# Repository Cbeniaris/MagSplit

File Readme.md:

# MagSplit
A wired split keyboard with ATmega32u4 promicro microcontrollers, oled displays, and magnetic connectors for module attachment

## Overview
MagSplit is an extension of my Beniaris46 keyboard featuring an extra column for each hand, much like a Corne board, and magnetic connectors for attaching "modules".  I made a few macropads that supported qmk and got frustrated when each one needed a new cable on my desk.   I wanted a modular system that allow attaching "modules" with different configuations for different workflows. Modules connect to the main keyboard via the magnetic connector on the side of the left split of the keyboard.  The magnetic connector handles ESD for the exposed pins as well as load switching for power delivery.  The modules themselves communicate over UART to the main half of the keyboard, notifying it of a successful connection, and relaying keypresses through to the host. Since each module is still a qmk board with the same ATmega32u4 micros, they still function as standalone HID boards. They retain their layers, macros, etc. when swapping hosts.  This allows for quickly snapping a new module on without needing to fetch a cable. 

## MODULE POWER WARNING
THERE IS NO BACK FEED PROTECTION FOR THE 5V RAIL.  You can plug in the usb and connect the module with the magnetic connector.  In an effort to keep complexity low and cost down, I did not include this.  The simple rule is: "One or the other". DO NOT attach both the magnetic connector to the main half of the keyboard AND the module to usb-c power at the same time. I had initially planned to use Schottky diodes to prevent this but worried about voltage drop for modules.

## Materials
| Component | Part Number |
| --- | --- |
| Micro | Any ATmega32ur pro micro |
| 3 pin TRS Jack | HC-PJ-320A-3P-D |
| Load Switch | TPS2552DBV (SOT-23-6, not WSON)|
| ESD protection | USBLC6-2SC6 |
| Switches | Any Cherry switches |
| Matrix Diodes | 1N4148W |
| Caps / Resistors | 0805 smd variants |
| Magnetic connectors | 2.54mm pitch from AliExpress|
| Oled Socket | 2.54mm pitch female socket|
| Oled Modules | Hosyond 0.96" I2C Oled Display |

## Compiling / Flashing

### Compiling
Firmware can be cloned and compiled using qmk or downloaded directly from the releases.

```bash
qmk compile -kb magsplit -km default
```

### Flashing

Flasing is done by putting the microcontroller into bootloader mode and using the qmk cli

```bash
qmk flash -kb magsplit -km default
```

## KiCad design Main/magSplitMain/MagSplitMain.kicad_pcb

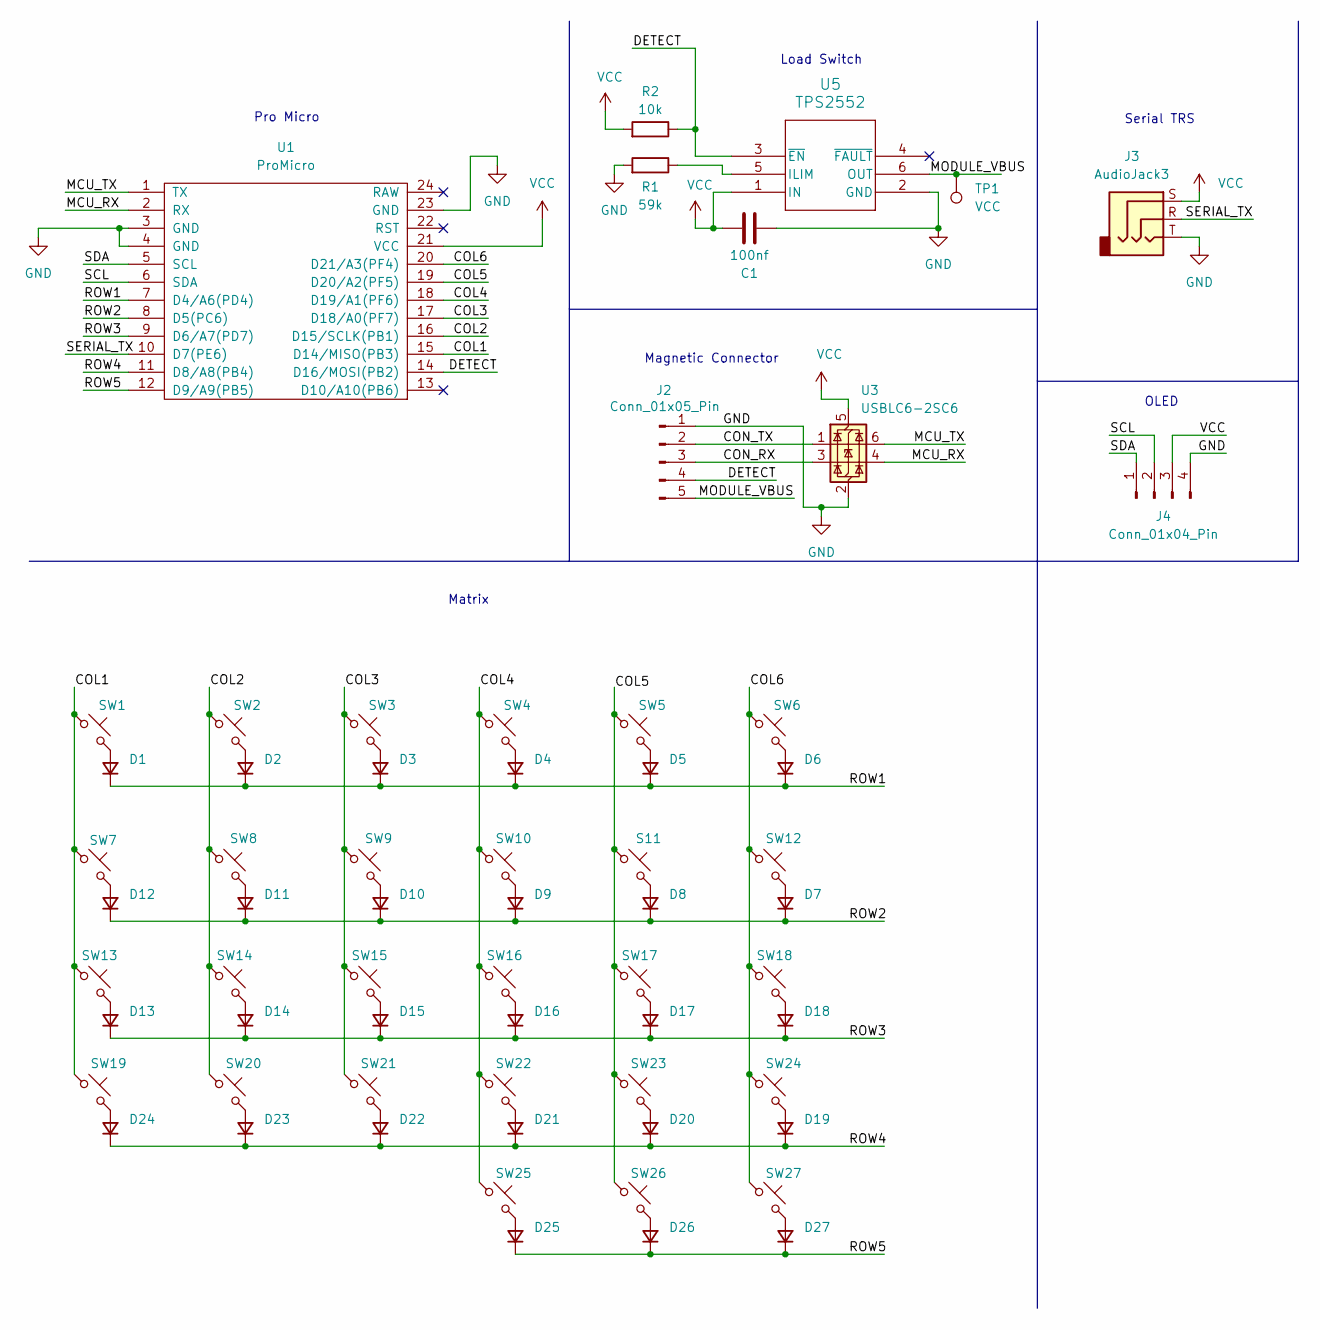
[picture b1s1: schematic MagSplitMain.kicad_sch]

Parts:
C1: 100nf; C_0805_2012Metric_Pad1.18x1.45mm_HandSolder
D1, D2, D3, D4, D5, D6, D7, D8, D9, D10, D11, D12, D13, D14, D15, D16, D17, D18, D19, D20, D21, D22, D23, D24, D25, D26, D27: D_Small; D_SOD-123
J2: Conn_01x05_Pin; PinHeader_1x05_P2.54mm_Vertical
J3: AudioJack3; HC-PJ-320A-3P-D
J4: Conn_01x04_Pin; PinSocket_1x04_P2.54mm_Vertical
R1: 59k; C_0805_2012Metric_Pad1.18x1.45mm_HandSolder
R2: 10k; C_0805_2012Metric_Pad1.18x1.45mm_HandSolder
S11: SW_Push_45deg; SW_Cherry_MX_1.00u_PCB
SW1, SW2, SW3, SW4, SW5, SW6, SW7, SW8, SW9, SW10, SW12, SW13, SW14, SW15, SW16, SW17, SW18, SW19, SW20, SW21, SW22, SW23, SW24, SW25, SW26, SW27: SW_Push_45deg; SW_Cherry_MX_1.00u_PCB
TP1: VCC
U1: ProMicro
U3: USBLC6-2SC6; SOT-23-6
U5: TPS2552; SOT-23-6_Handsoldering

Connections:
/COL1: SW1.1, SW7.1, SW13.1, SW19.1, U1.15 (D14/MISO(PB3))
/COL2: SW2.1, SW8.1, SW14.1, SW20.1, U1.16 (D15/SCLK(PB1))
/COL3: SW3.1, SW9.1, SW15.1, SW21.1, U1.17 (D18/A0(PF7))
/COL4: SW4.1, SW10.1, SW16.1, SW22.1, SW25.1, U1.18 (D19/A1(PF6))
/COL5: S11.1, SW5.1, SW17.1, SW23.1, SW26.1, U1.19 (D20/A2(PF5))
/COL6: SW6.1, SW12.1, SW18.1, SW24.1, SW27.1, U1.20 (D21/A3(PF4))
/CON_RX: J2.3, U3.3 (I/O2)
/CON_TX: J2.2, U3.1 (I/O1)
/DETECT: J2.4, R2.1, U1.14 (D16/MOSI(PB2)), U5.3 (~EN)
/MCU_RX: U1.2 (RX), U3.4 (I/O2)
/MCU_TX: U1.1 (TX), U3.6 (I/O1)
/MODULE_VBUS: J2.5, TP1.1, U5.6 (OUT)
/ROW1: D1.1 (K), D2.1 (K), D3.1 (K), D4.1 (K), D5.1 (K), D6.1 (K), U1.7 (D4/A6(PD4))
/ROW2: D7.1 (K), D8.1 (K), D9.1 (K), D10.1 (K), D11.1 (K), D12.1 (K), U1.8 (D5(PC6))
/ROW3: D13.1 (K), D14.1 (K), D15.1 (K), D16.1 (K), D17.1 (K), D18.1 (K), U1.9 (D6/A7(PD7))
/ROW4: D19.1 (K), D20.1 (K), D21.1 (K), D22.1 (K), D23.1 (K), D24.1 (K), U1.11 (D8/A8(PB4))
/ROW5: D25.1 (K), D26.1 (K), D27.1 (K), U1.12 (D9/A9(PB5))
/SCL: J4.2, U1.6 (SDA)
/SDA: J4.1, U1.5 (SCL)
/SERIAL_TX: J3.R, U1.10 (D7(PE6))
GND: C1.2, J2.1, J3.T, J4.4, R1.2, U1.3 (GND), U1.4 (GND), U1.23 (GND), U3.2 (GND), U5.2 (GND)
unnamed: D1.2 (A), SW1.2
unnamed: D2.2 (A), SW2.2
unnamed: D3.2 (A), SW3.2
unnamed: D4.2 (A), SW4.2
unnamed: D5.2 (A), SW5.2
unnamed: D6.2 (A), SW6.2
unnamed: D7.2 (A), SW12.2
unnamed: D8.2 (A), S11.2
unnamed: D9.2 (A), SW10.2
unnamed: D10.2 (A), SW9.2
unnamed: D11.2 (A), SW8.2
unnamed: D12.2 (A), SW7.2
unnamed: D13.2 (A), SW13.2
unnamed: D14.2 (A), SW14.2
unnamed: D15.2 (A), SW15.2
unnamed: D16.2 (A), SW16.2
unnamed: D17.2 (A), SW17.2
unnamed: D18.2 (A), SW18.2
unnamed: D19.2 (A), SW24.2
unnamed: D20.2 (A), SW23.2
unnamed: D21.2 (A), SW22.2
unnamed: D22.2 (A), SW21.2
unnamed: D23.2 (A), SW20.2
unnamed: D24.2 (A), SW19.2
unnamed: D25.2 (A), SW25.2
unnamed: D26.2 (A), SW26.2
unnamed: D27.2 (A), SW27.2
unnamed: R1.1, U5.5 (ILIM)
VCC: C1.1, J3.S, J4.3, R2.2, U1.21 (VCC), U3.5 (VBUS), U5.1 (IN)

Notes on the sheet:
Load Switch
Matrix
Pro Micro
OLED
Serial TRS
Magnetic Connector

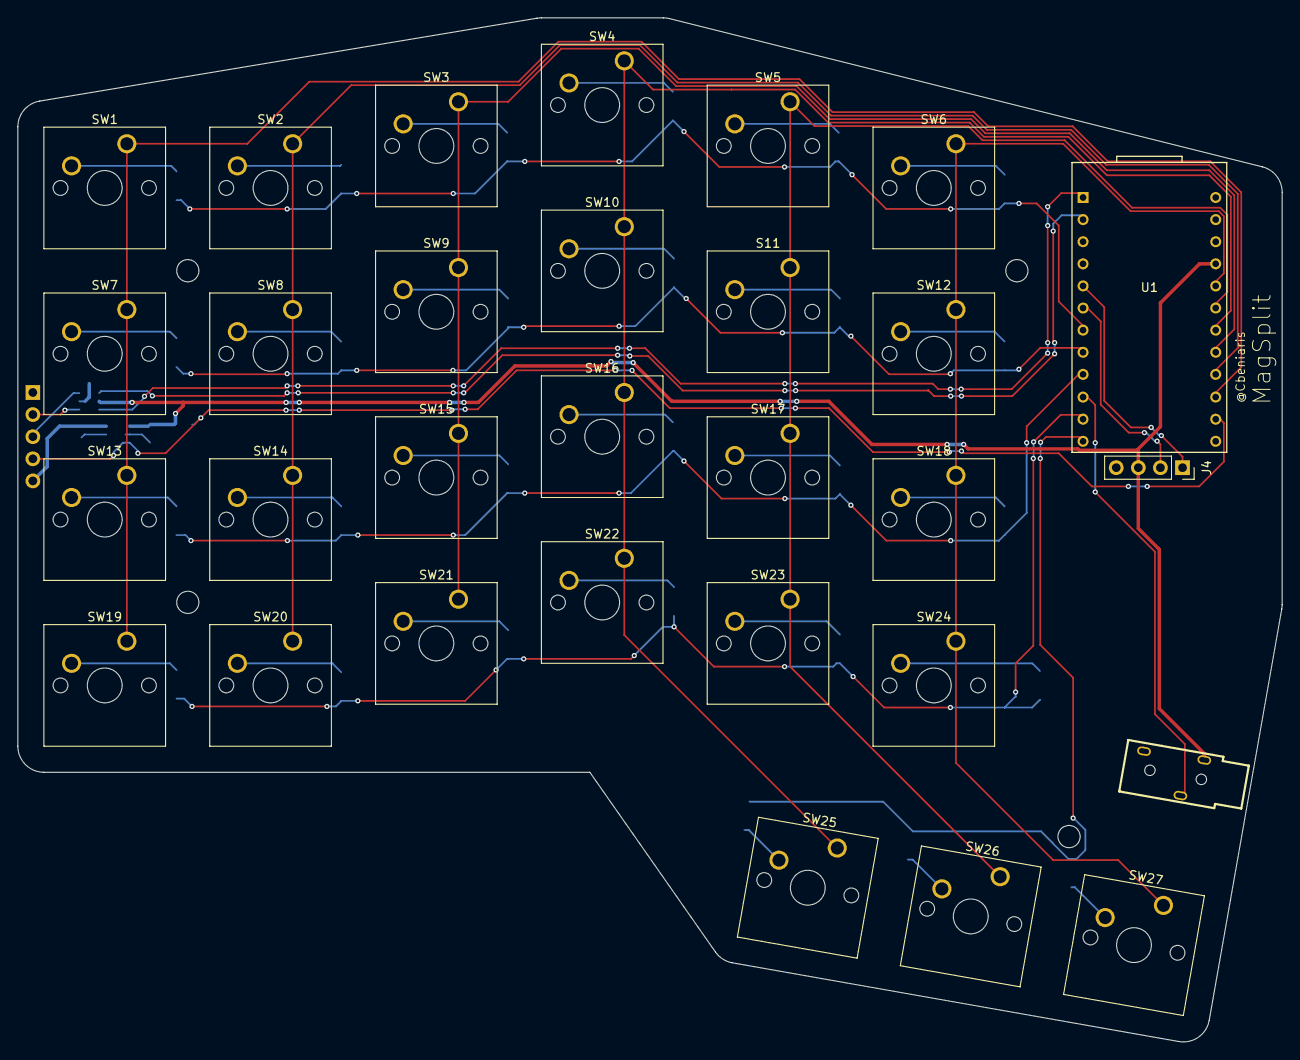
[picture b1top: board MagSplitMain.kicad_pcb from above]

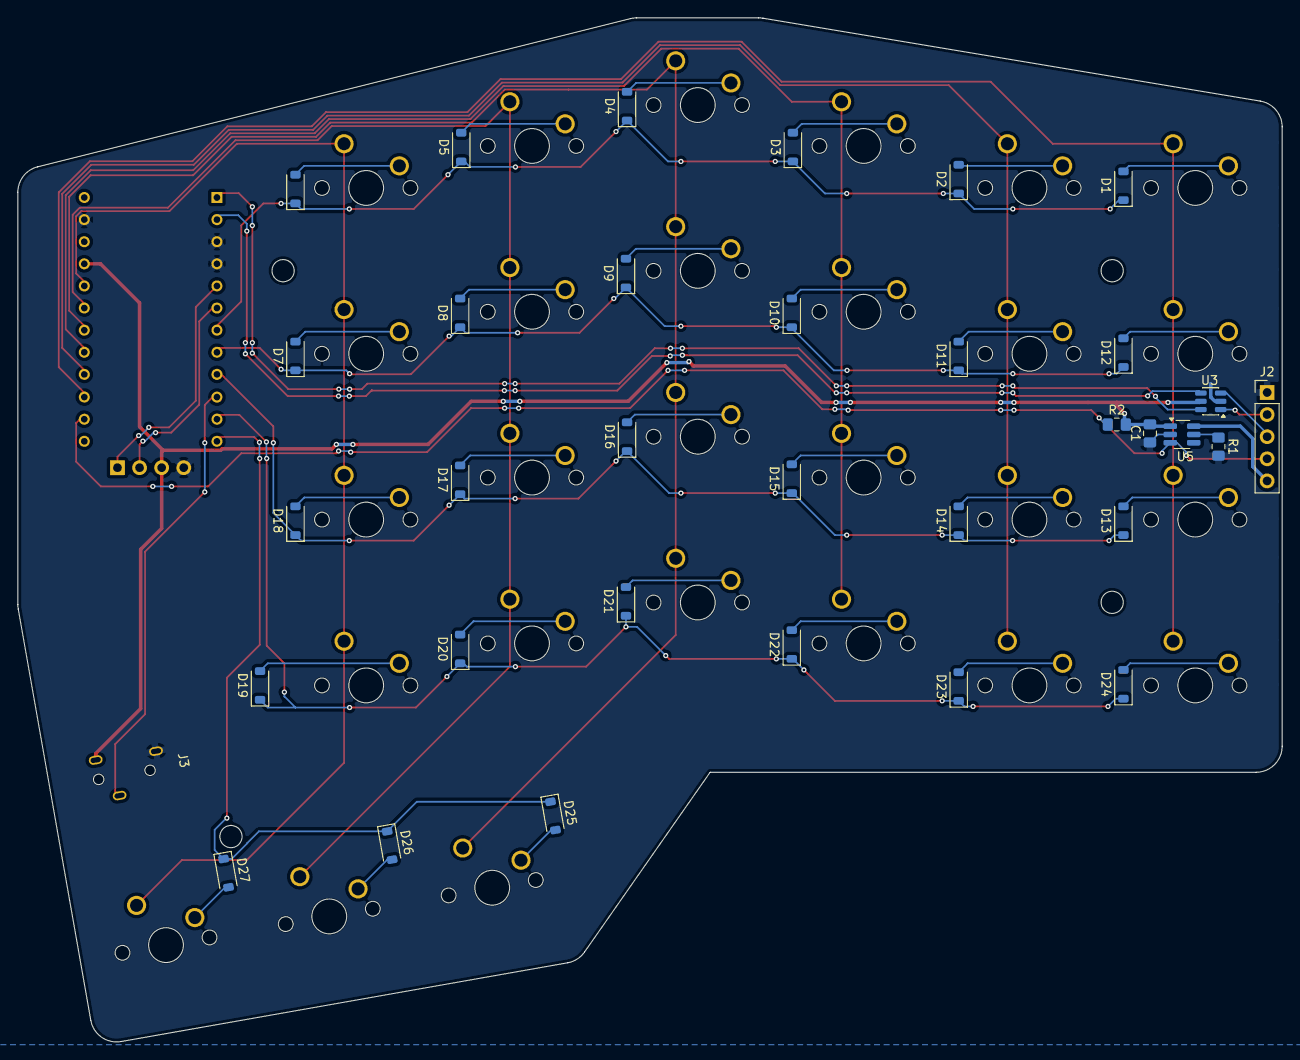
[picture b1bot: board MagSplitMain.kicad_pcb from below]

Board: 2 copper layers, 145.2 x 117.6 mm, 63 parts (33 on the bottom side), 50 nets.

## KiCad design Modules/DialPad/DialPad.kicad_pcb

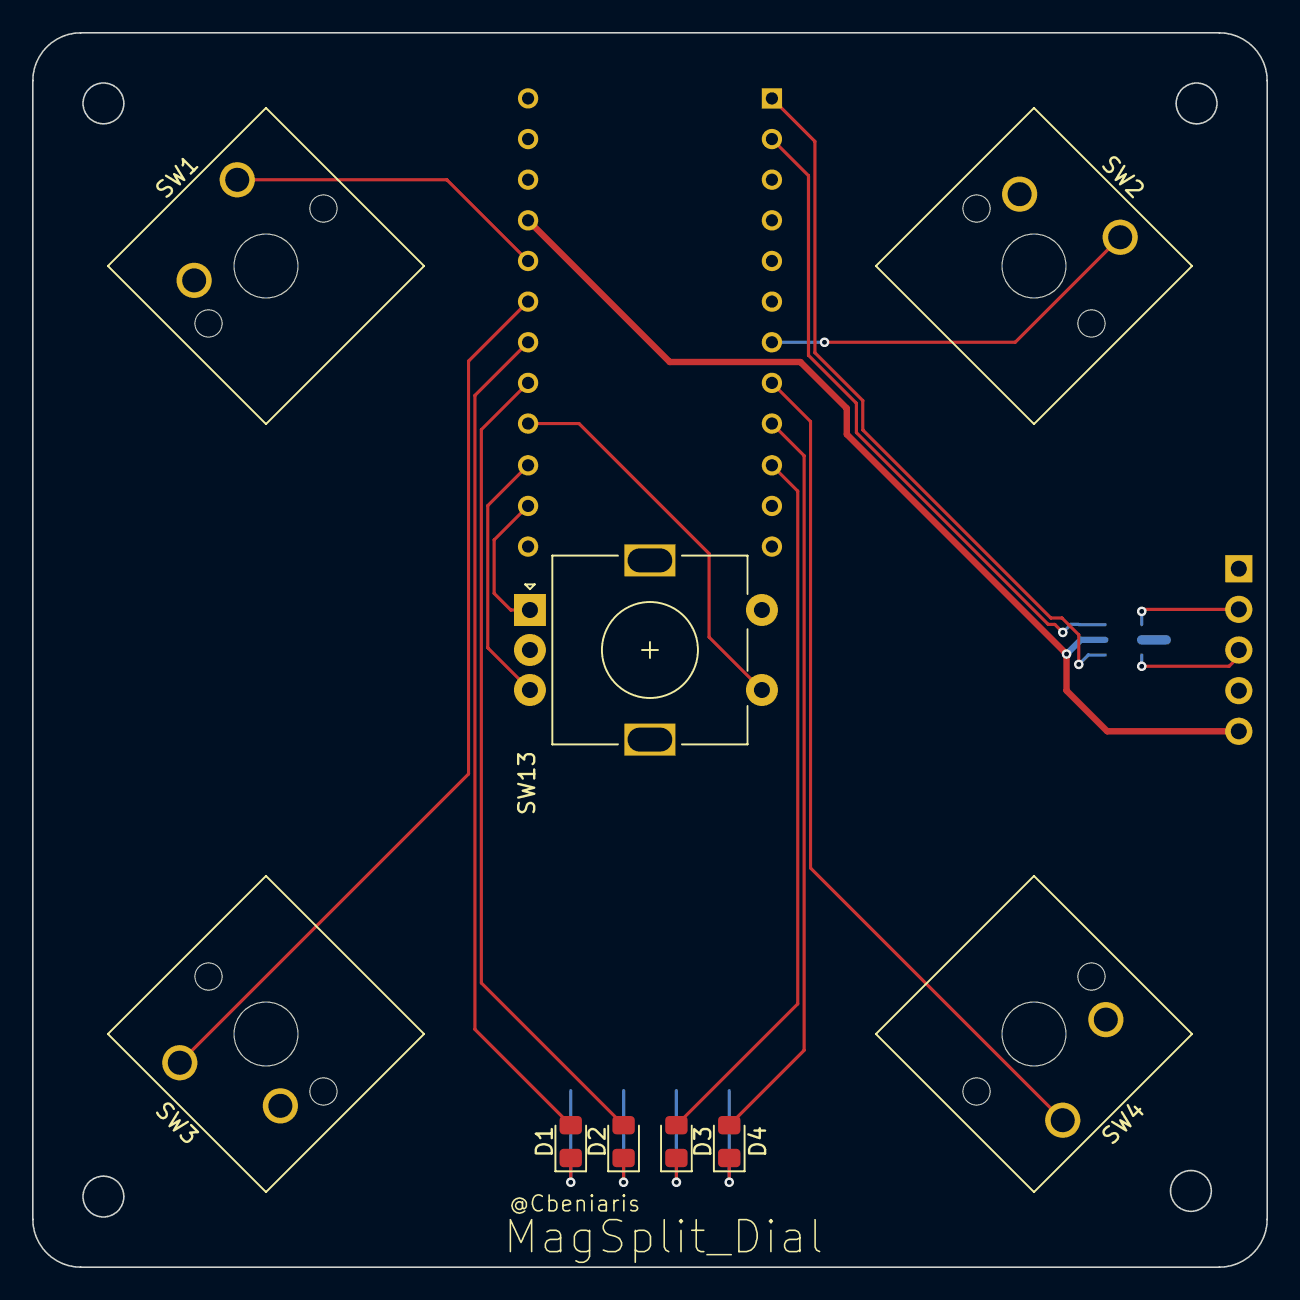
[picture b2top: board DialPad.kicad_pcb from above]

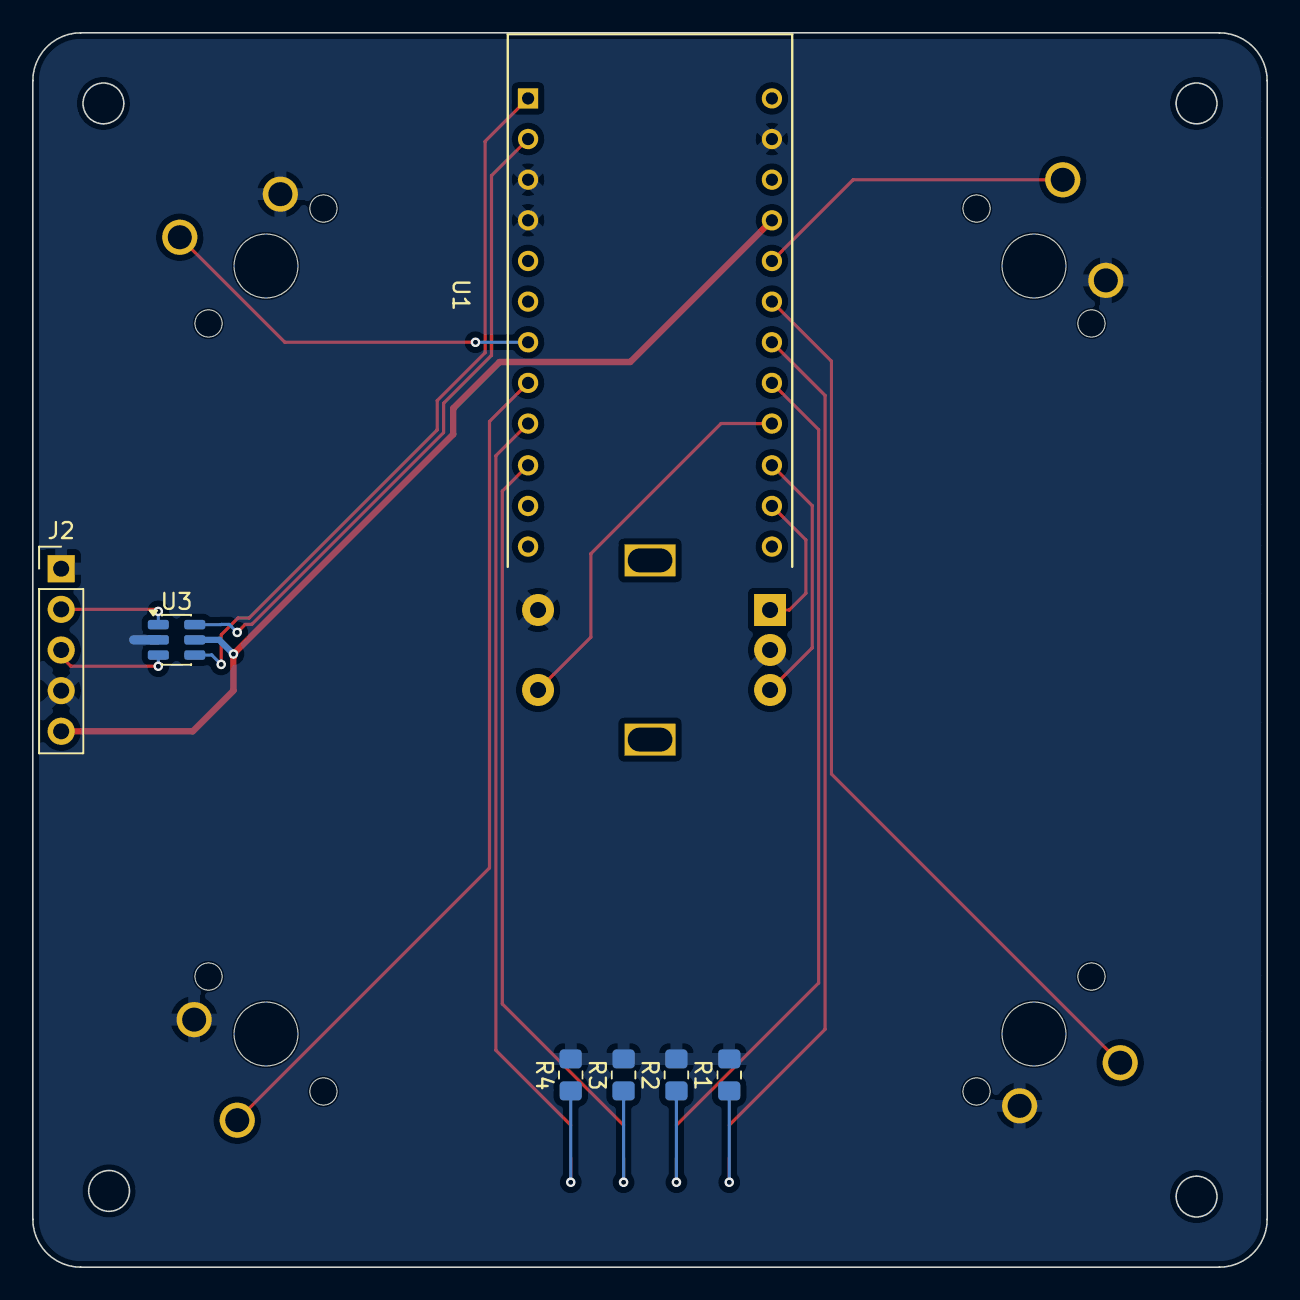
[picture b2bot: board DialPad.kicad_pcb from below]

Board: 2 copper layers, 77.1 x 77.1 mm, 16 parts (7 on the bottom side), 21 nets.

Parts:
D1: L1; LED_0805_2012Metric_Pad1.15x1.40mm_HandSolder
D2: L2; LED_0805_2012Metric_Pad1.15x1.40mm_HandSolder
D3: L3; LED_0805_2012Metric_Pad1.15x1.40mm_HandSolder
D4: L4; LED_0805_2012Metric_Pad1.15x1.40mm_HandSolder
J2: Conn_01x05_Pin; PinHeader_1x05_P2.54mm_Vertical
R1, R2, R3, R4: R_Small; R_0805_2012Metric_Pad1.20x1.40mm_HandSolder
SW1, SW2, SW3, SW4: SW_Push_45deg; SW_Cherry_MX_1.00u_PCB
SW13: RotaryEncoder_Switch; RotaryEncoder_Alps_EC11E-Switch_Vertical_H20mm
U1: ProMicro
U3: USBLC6-2SC6; SOT-23-6

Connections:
/CON_RX: J2.3, U3.3 (I/O2)
/CON_TX: J2.2, U3.1 (I/O1)
/ENC_A: SW13.A, U1.14 (D16/MOSI(PB2))
/ENC_B: SW13.B, U1.15 (D14/MISO(PB3))
/ENC_SW: SW13.S1, U1.16 (D15/SCLK(PB1))
/KEY1: SW1.1, U1.20 (D21/A3(PF4))
/KEY2: SW2.1, U1.7 (D4/A6(PD4))
/KEY3: SW3.1, U1.19 (D20/A2(PF5))
/KEY4: SW4.1, U1.8 (D5(PC6))
/L1_RESISTOR: D1.1 (K), R1.1
/L2_RESISTOR: D2.1 (K), R2.1
/L3_RESISTOR: D3.1 (K), R3.1
/L4_RESISTOR: D4.1 (K), R4.1
/LAYER1: D1.2 (A), U1.18 (D19/A1(PF6))
/LAYER2: D2.2 (A), U1.17 (D18/A0(PF7))
/LAYER3: D3.2 (A), U1.10 (D7(PE6))
/LAYER4: D4.2 (A), U1.9 (D6/A7(PD7))
/MCU_RX: U1.2 (RX), U3.6 (I/O1)
/MCU_TX: U1.1 (TX), U3.4 (I/O2)
GND: J2.1, J2.4, R1.2, R2.2, R3.2, R4.2, SW1.2, SW2.2, SW3.2, SW4.2, SW13.C, SW13.S2, U1.3 (GND), U1.4 (GND), U1.23 (GND), U3.2 (GND)
VCC: J2.5, U1.21 (VCC), U3.5 (VBUS)

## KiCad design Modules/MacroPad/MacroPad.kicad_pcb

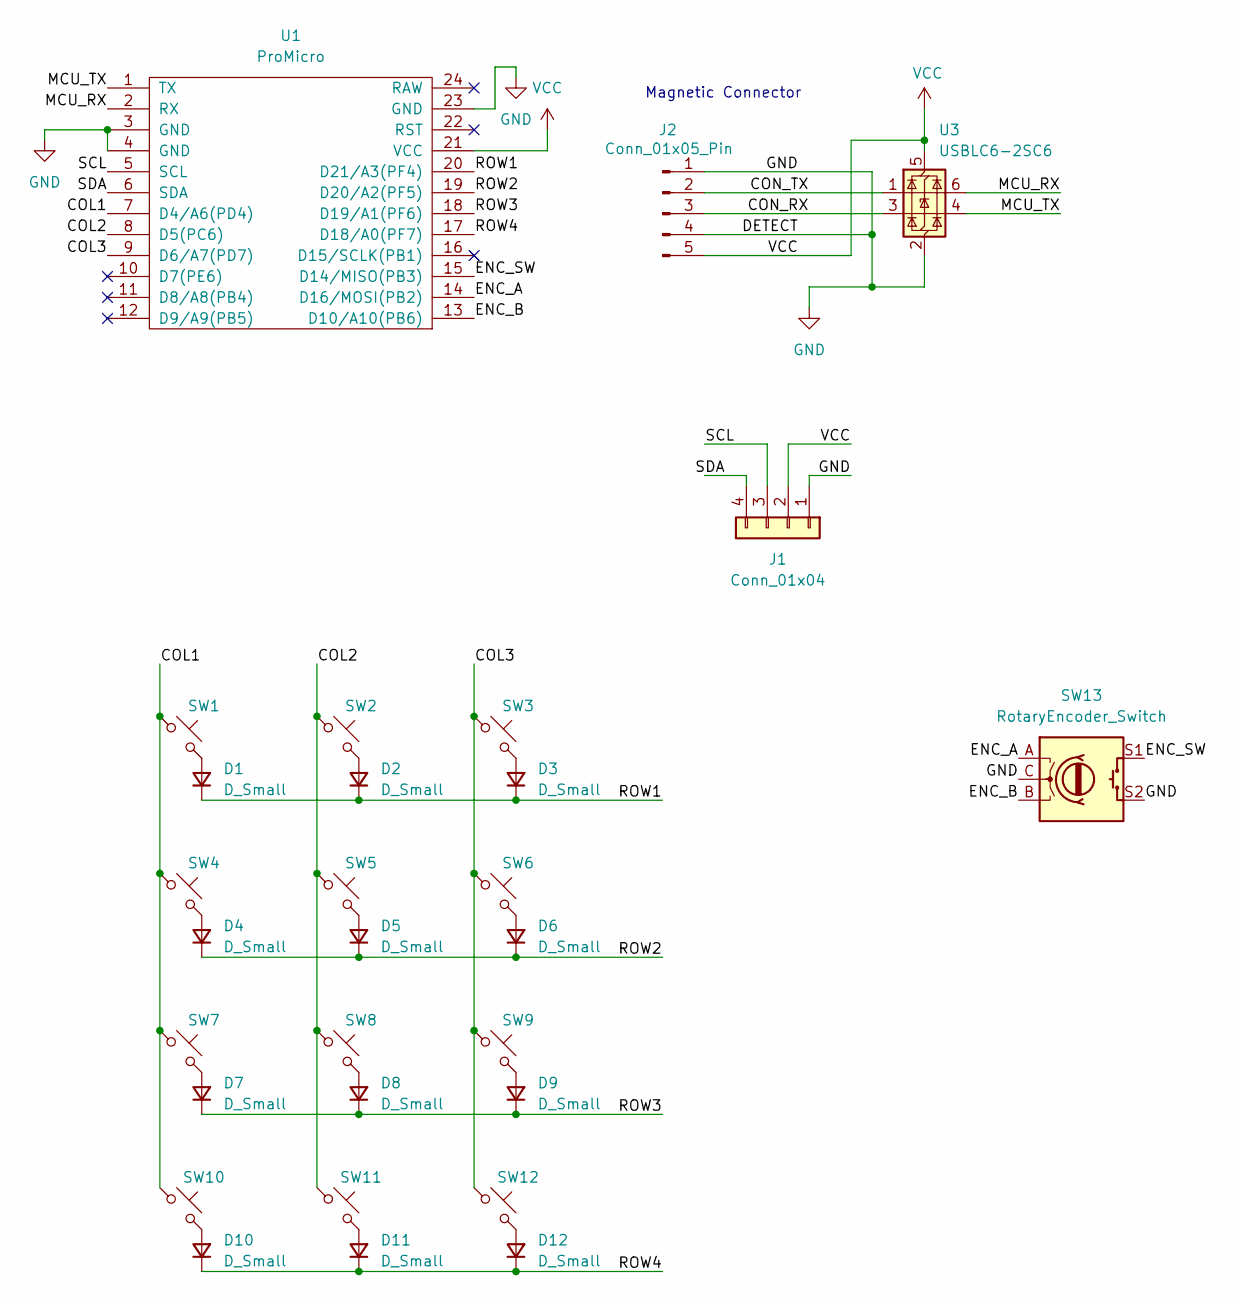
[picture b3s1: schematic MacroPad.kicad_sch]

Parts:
D1, D2, D3, D4, D5, D6, D7, D8, D9, D10, D11, D12: D_Small; D_SOD-123
J1: Conn_01x04; PinSocket_1x04_P2.54mm_Vertical
J2: Conn_01x05_Pin; PinHeader_1x05_P2.54mm_Vertical
SW1, SW2, SW3, SW4, SW5, SW6, SW7, SW8, SW9, SW10, SW11, SW12: SW_Push_45deg; SW_Cherry_MX_1.00u_PCB
SW13: RotaryEncoder_Switch; RotaryEncoder_Alps_EC11E-Switch_Vertical_H20mm
U1: ProMicro
U3: USBLC6-2SC6; SOT-23-6

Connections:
/COL1: SW1.1, SW4.1, SW7.1, SW10.1, U1.7 (D4/A6(PD4))
/COL2: SW2.1, SW5.1, SW8.1, SW11.1, U1.8 (D5(PC6))
/COL3: SW3.1, SW6.1, SW9.1, SW12.1, U1.9 (D6/A7(PD7))
/CON_RX: J2.3, U3.3 (I/O2)
/CON_TX: J2.2, U3.1 (I/O1)
/ENC_A: SW13.A, U1.14 (D16/MOSI(PB2))
/ENC_B: SW13.B, U1.13 (D10/A10(PB6))
/ENC_SW: SW13.S1, U1.15 (D14/MISO(PB3))
/MCU_RX: U1.2 (RX), U3.6 (I/O1)
/MCU_TX: U1.1 (TX), U3.4 (I/O2)
/ROW1: D1.1 (K), D2.1 (K), D3.1 (K), U1.20 (D21/A3(PF4))
/ROW2: D4.1 (K), D5.1 (K), D6.1 (K), U1.19 (D20/A2(PF5))
/ROW3: D7.1 (K), D8.1 (K), D9.1 (K), U1.18 (D19/A1(PF6))
/ROW4: D10.1 (K), D11.1 (K), D12.1 (K), U1.17 (D18/A0(PF7))
/SCL: J1.3, U1.5 (SCL)
/SDA: J1.4, U1.6 (SDA)
GND: J1.1, J2.1, J2.4, SW13.C, SW13.S2, U1.3 (GND), U1.4 (GND), U1.23 (GND), U3.2 (GND)
unnamed: D1.2 (A), SW1.2
unnamed: D2.2 (A), SW2.2
unnamed: D3.2 (A), SW3.2
unnamed: D4.2 (A), SW4.2
unnamed: D5.2 (A), SW5.2
unnamed: D6.2 (A), SW6.2
unnamed: D7.2 (A), SW7.2
unnamed: D8.2 (A), SW8.2
unnamed: D9.2 (A), SW9.2
unnamed: D10.2 (A), SW10.2
unnamed: D11.2 (A), SW11.2
unnamed: D12.2 (A), SW12.2
VCC: J1.2, J2.5, U1.21 (VCC), U3.5 (VBUS)

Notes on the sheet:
Magnetic Connector

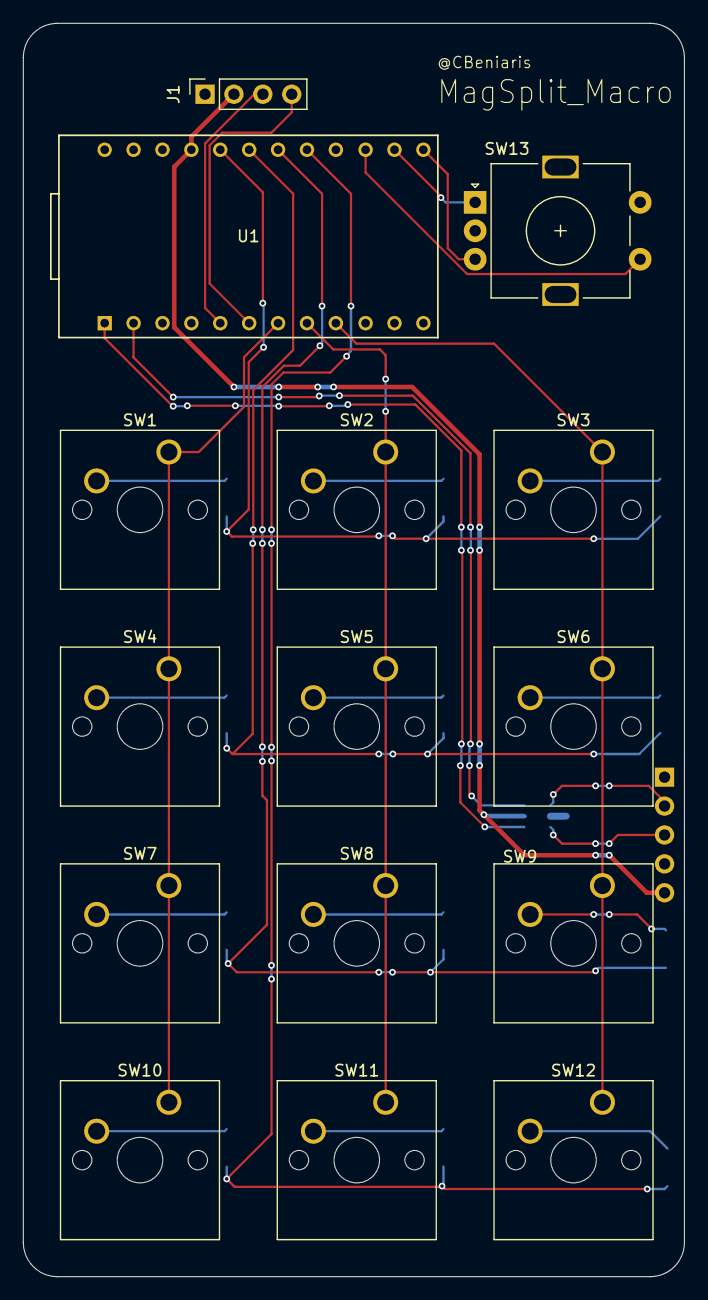
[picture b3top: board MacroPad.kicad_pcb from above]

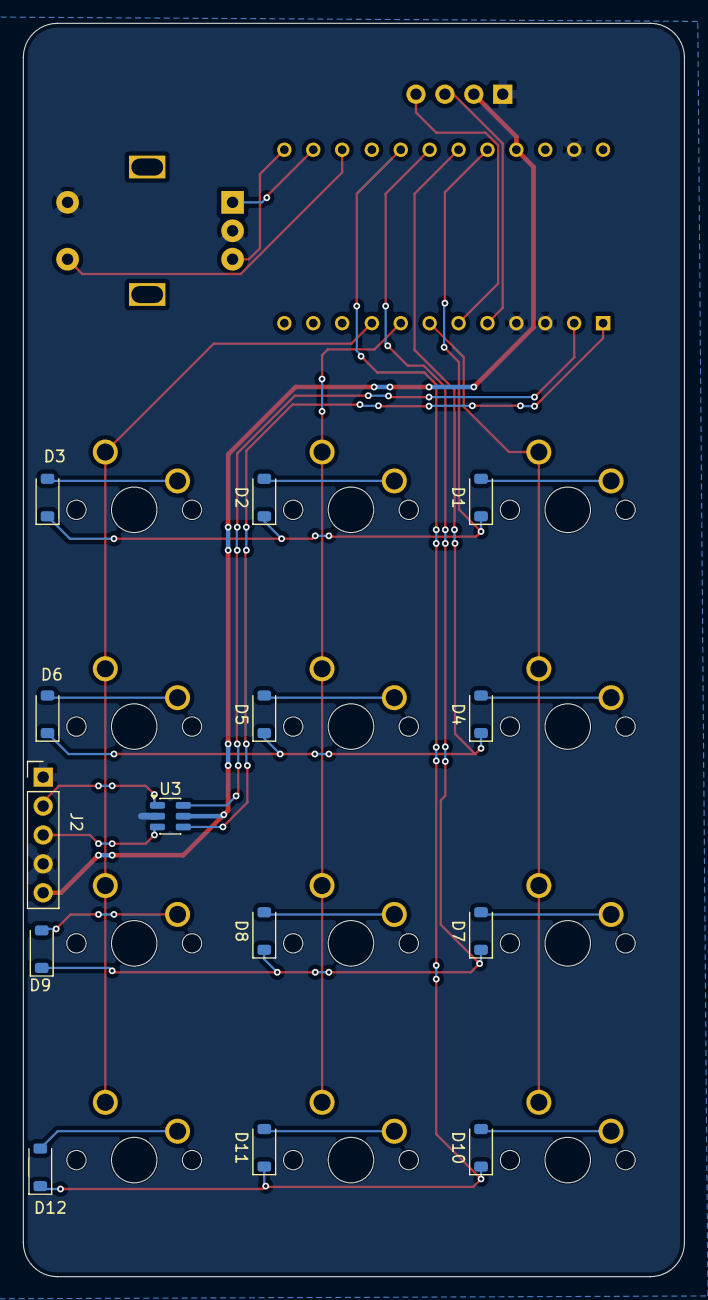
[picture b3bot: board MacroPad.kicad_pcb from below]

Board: 2 copper layers, 58.1 x 110.1 mm, 29 parts (14 on the bottom side), 30 nets.
